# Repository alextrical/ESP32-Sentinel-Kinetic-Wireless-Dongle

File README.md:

# ESP32-Vent-Axia-Sentinel-Kinetic-Wired-Remote-Dongle
ESP32 based Re-implementation of the Vent-Axia Sentinel Kinetic Wired Remote Controller
Arduino sketch can be simulated here
https://wokwi.com/projects/427157112827024385

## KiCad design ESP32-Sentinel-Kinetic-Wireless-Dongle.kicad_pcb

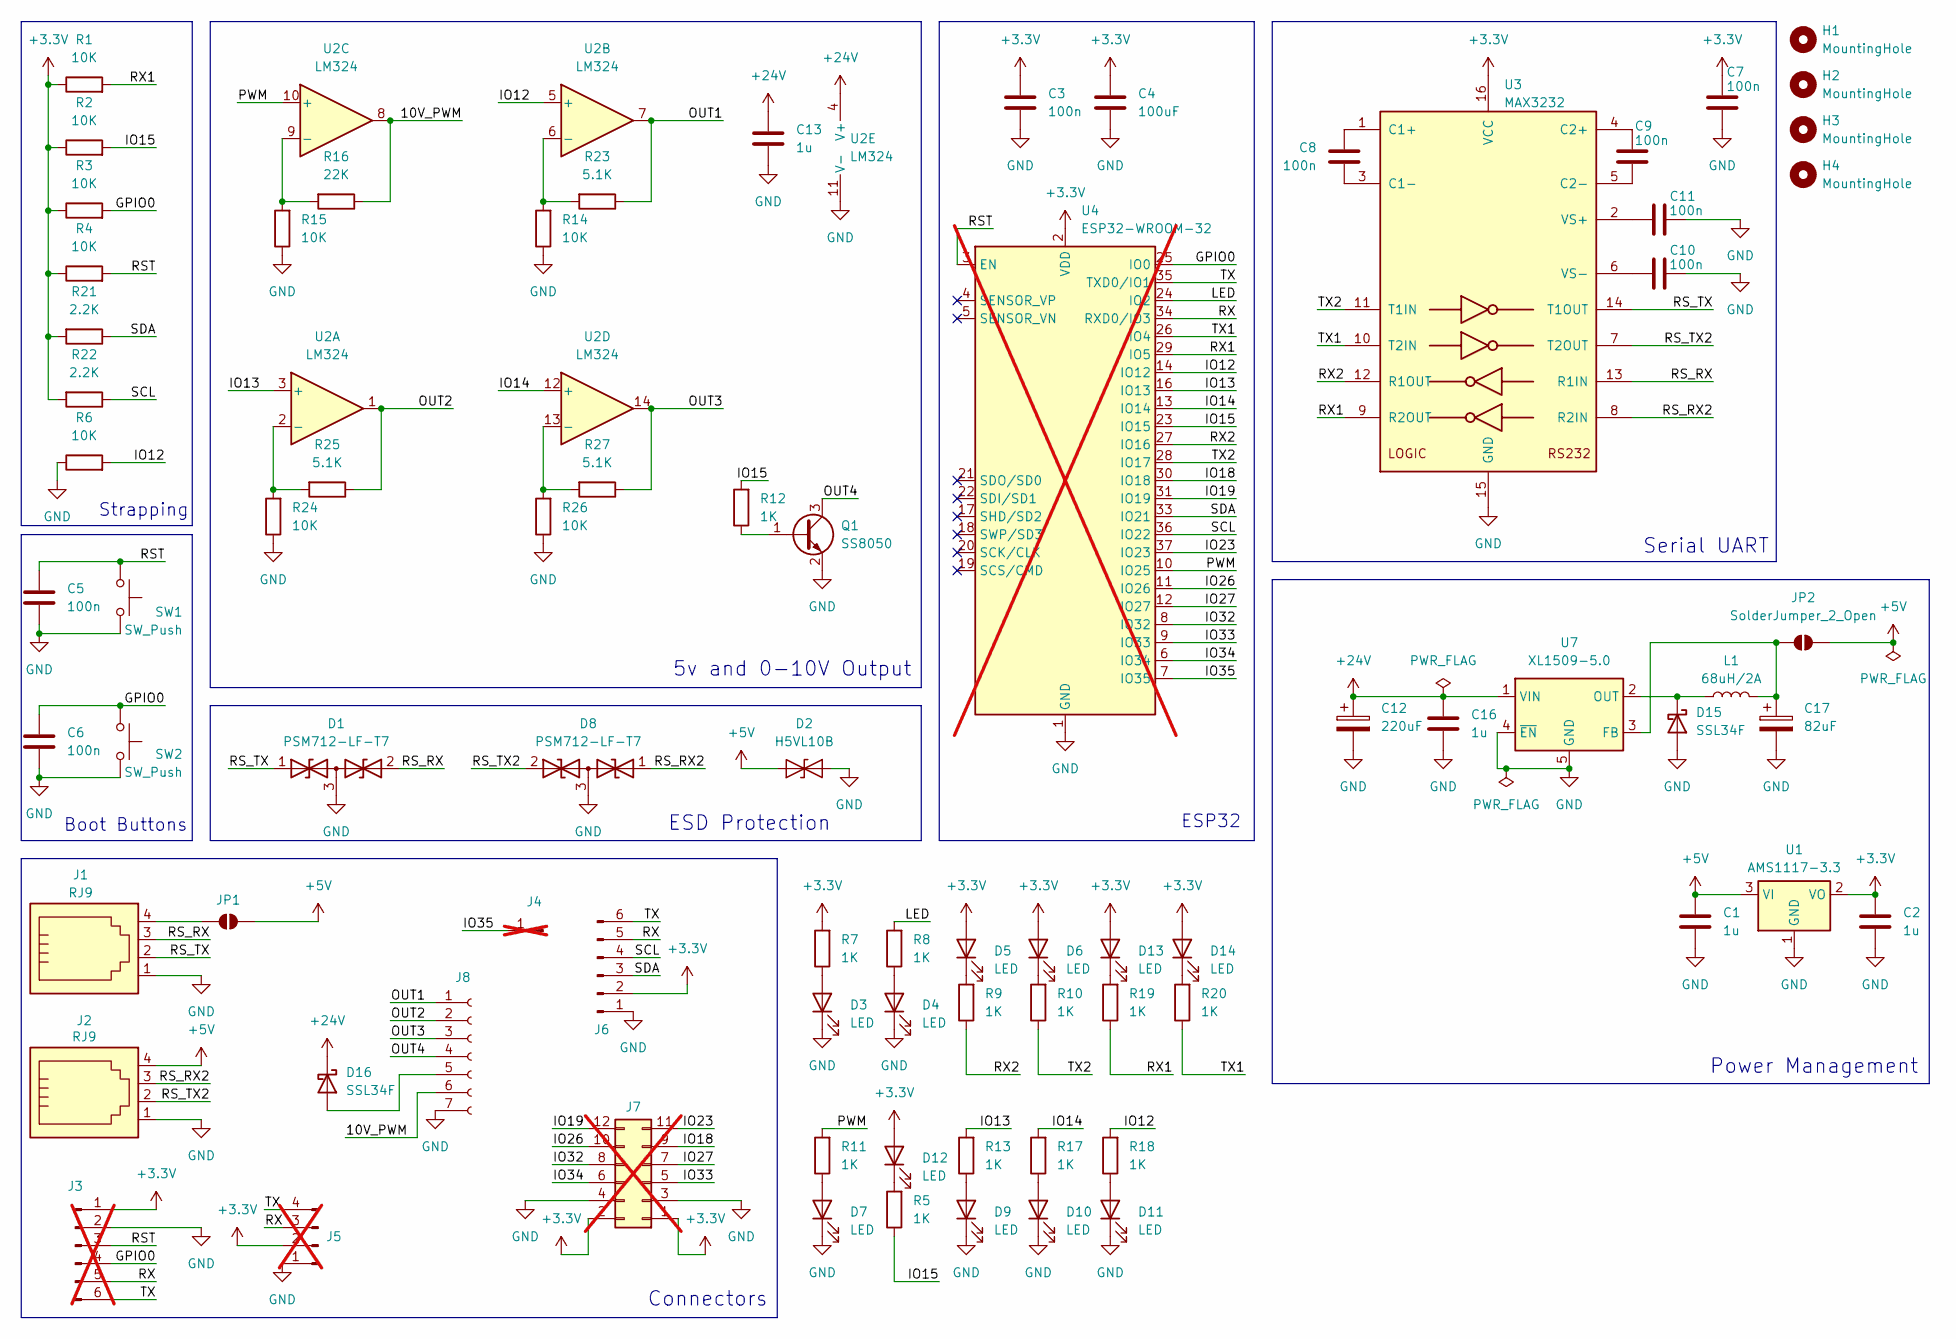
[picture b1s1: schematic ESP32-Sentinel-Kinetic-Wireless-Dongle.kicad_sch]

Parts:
C1, C2: 1u; C_0402_1005Metric; LCSC C52923
C3, C5, C6, C7, C8, C9, C10, C11: 100n; C_0402_1005Metric; LCSC C307331
C4: 100uF; C_1206_3216Metric; LCSC C15008
C12: 220uF; CP_Radial_D10.0mm_P5.00mm
C13, C16: 1u; C_1206_3216Metric; LCSC C1848
C17: 82uF; CP_Radial_D10.0mm_P2.50mm_P5.00mm
D1, D8: PSM712-LF-T7; SOT-23; LCSC C32677
D2: H5VL10B; D_SOD-882; LCSC C7420372
D3, D4, D5, D6, D7, D9, D10, D11, D12, D13, D14: LED; LED_0603_1608Metric; LCSC C2286
D15, D16: SSL34F; D_SMA; LCSC C28646282
H1, H2, H3, H4: MountingHole; MountingHole_3.2mm_M3
J1, J2: RJ9; RJ9-TH-623K-4P4CGRAYBOUNDLESS
J3: Conn_01x06_Pin; PinHeader_1x06_P2.00mm_Vertical_locking; not fitted
J4: Conn_01x01_Pin; PinHeader_1x01_P2.54mm_Vertical; not fitted
J5: Conn_01x04_Pin; PinHeader_1x04_P2.54mm_Vertical; not fitted
J6: Conn_01x06_Pin; JST_XH_B6B-XH-A_1x06_P2.50mm_Vertical
J7: Conn_02x06_Odd_Even; PinHeader_2x06_P2.54mm_Vertical; not fitted
J8: Conn_01x07_Socket; JST_XH_B7B-XH-A_1x07_P2.50mm_Vertical
JP1, JP2: SolderJumper_2_Open; SolderJumper-2_P1.3mm_Open_RoundedPad1.0x1.5mm
L1: 68uH/2A; L_APV_APH0850; LCSC C41415633
Q1: SS8050; SOT-23; LCSC C431710
R1, R2, R3, R4, R6, R14, R15, R24, R26: 10K; R_0402_1005Metric; LCSC C25744
R5, R7, R8, R9, R10, R11, R12, R13, R17, R18, R19, R20: 1K; R_0402_1005Metric; LCSC C11702
R16: 22K; R_0402_1005Metric; LCSC C25768
R21, R22: 2.2K; R_0402_1005Metric; LCSC C25879
R23, R25, R27: 5.1K; R_0402_1005Metric; LCSC C25905
SW1, SW2: SW_Push; SW_Push_1P1T_XKB_TS-1187A; LCSC C318884
U1: AMS1117-3.3; SOT-223-3_TabPin2; LCSC C6186
U2: LM324; SOIC-14_3.9x8.7mm_P1.27mm; LCSC C71035
U3: MAX3232; SOP-16_3.9x9.9mm_P1.27mm; LCSC C5201633
U4: ESP32-WROOM-32; not fitted
U7: XL1509-5.0; SOIC-8_3.9x4.9mm_P1.27mm; LCSC C61063

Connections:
+3.3V: C2.1, C3.1, C4.1, C7.1, D5.2 (A), D6.2 (A), D12.2 (A), D13.2 (A), D14.2 (A), J3.1, J5.2, J6.2, J7.1, J7.2, R1.1, R2.1, R3.1, R4.1, R7.2, R21.2, R22.2, U1.2 (VO), U3.16 (VCC), U4.2 (VDD)
+5V: C1.1, D2.1 (A1), J2.4, JP1.2 (B), JP2.2 (B), U1.3 (VI)
+24V: C12.1, C13.1, C16.1, D16.1 (K), U2.4 (V+), U7.1 (VIN)
/10V_PWM: J8.6, R16.1, U2.8
/GPIO0: C6.1, J3.4, R3.2, SW2.1, U4.25 (IO0)
/IO12: R6.2, R18.2, U2.5 (+), U4.14 (IO12)
/IO13: R13.2, U2.3 (+), U4.16 (IO13)
/IO14: R17.2, U2.12 (+), U4.13 (IO14)
/IO15: R2.2, R5.1, R12.2, U4.23 (IO15)
/IO18: J7.9, U4.30 (IO18)
/IO19: J7.12, U4.31 (IO19)
/IO23: J7.11, U4.37 (IO23)
/IO26: J7.10, U4.11 (IO26)
/IO27: J7.7, U4.12 (IO27)
/IO32: J7.8, U4.8 (IO32)
/IO33: J7.5, U4.9 (IO33)
/IO34: J7.6, U4.6 (IO34)
/IO35: J4.1, U4.7 (IO35)
/LED: R8.2, U4.24 (IO2)
/OUT1: J8.1, R23.1, U2.7
/OUT2: J8.2, R25.1, U2.1
/OUT3: J8.3, R27.1, U2.14
/OUT4: J8.4, Q1.3 (C)
/PWM: R11.2, U2.10 (+), U4.10 (IO25)
/RST: C5.1, J3.3, R4.2, SW1.1, U4.3 (EN)
/RS_RX: D1.2 (A2), J1.3, U3.13 (R1IN)
/RS_RX2: D8.1 (A1), J2.3, U3.8 (R2IN)
/RS_TX: D1.1 (A1), J1.2, U3.14 (T1OUT)
/RS_TX2: D8.2 (A2), J2.2, U3.7 (T2OUT)
/RX: J3.5, J5.3, J6.5, U4.34 (RXD0/IO3)
/RX1: R1.2, R19.1, U3.9 (R2OUT), U4.29 (IO5)
/RX2: R9.1, U3.12 (R1OUT), U4.27 (IO16)
/SCL: J6.4, R22.1, U4.36 (IO22)
/SDA: J6.3, R21.1, U4.33 (IO21)
/TX: J3.6, J5.4, J6.6, U4.35 (TXD0/IO1)
/TX1: R20.1, U3.10 (T2IN), U4.26 (IO4)
/TX2: R10.1, U3.11 (T1IN), U4.28 (IO17)
GND: C1.2, C2.2, C3.2, C4.2, C5.2, C6.2, C7.2, C10.2, C11.2, C12.2, C13.2, C16.2, C17.2, D1.3 (common), D2.2 (A2), D3.1 (K), D4.1 (K), D7.1 (K), D8.3 (common), D9.1 (K), D10.1 (K), D11.1 (K), D15.2 (A), J1.1, J2.1, J3.2, J5.1, J6.1, J7.3, J7.4, J8.7, Q1.2 (E), R6.1, R14.1, R15.1, R24.1, R26.1, SW1.2, SW2.2, U1.1 (GND), U2.11 (V-), U3.15 (GND), U4.1 (GND), U4.15 (GND), U4.38 (GND), U4.39 (GND), U7.4 (~EN), U7.5 (GND), U7.6 (GND), U7.7 (GND), U7.8 (GND)
unnamed: D3.2 (A), R7.1
unnamed: D4.2 (A), R8.1
unnamed: D5.1 (K), R9.2
unnamed: D6.1 (K), R10.2
unnamed: D7.2 (A), R11.1
unnamed: D9.2 (A), R13.1
unnamed: D10.2 (A), R17.1
unnamed: D11.2 (A), R18.1
unnamed: D12.1 (K), R5.2
unnamed: D13.1 (K), R19.2
unnamed: D14.1 (K), R20.2
unnamed: D15.1 (K), L1.1, U7.2 (OUT)
unnamed: D16.2 (A), J8.5
unnamed: J1.4, JP1.1 (A)
unnamed: C17.1, JP2.1 (A), L1.2, U7.3 (FB)
unnamed: Q1.1 (B), R12.1
unnamed: R24.2, R25.2, U2.2 (-)
unnamed: R14.2, R23.2, U2.6 (-)
unnamed: R15.2, R16.2, U2.9 (-)
unnamed: R26.2, R27.2, U2.13 (-)
unnamed: C8.1, U3.1 (C1+)
unnamed: C8.2, U3.3 (C1-)
unnamed: C9.1, U3.4 (C2+)
unnamed: C9.2, U3.5 (C2-)
unnamed: C11.1, U3.2 (VS+)
unnamed: C10.1, U3.6 (VS-)

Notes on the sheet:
ESP32
5v and 0-10V Output
Boot Buttons
Strapping
Power Management
Serial UART
Connectors
ESD Protection

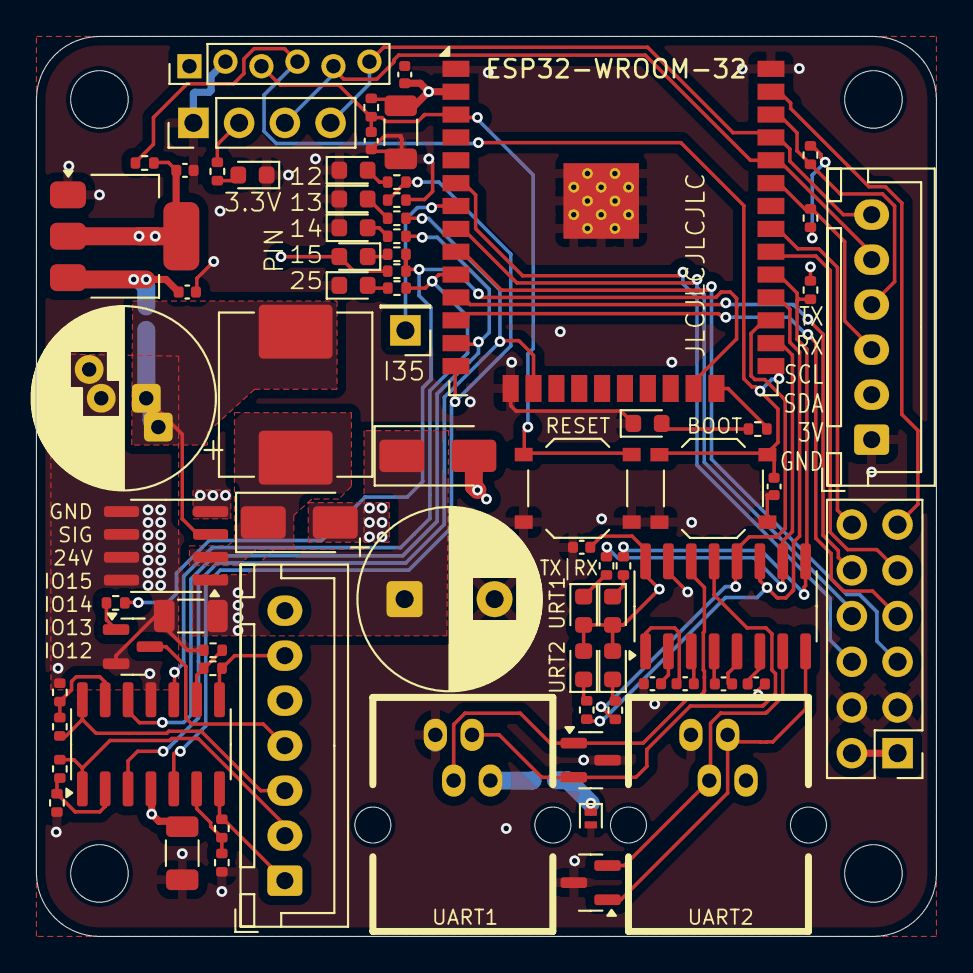
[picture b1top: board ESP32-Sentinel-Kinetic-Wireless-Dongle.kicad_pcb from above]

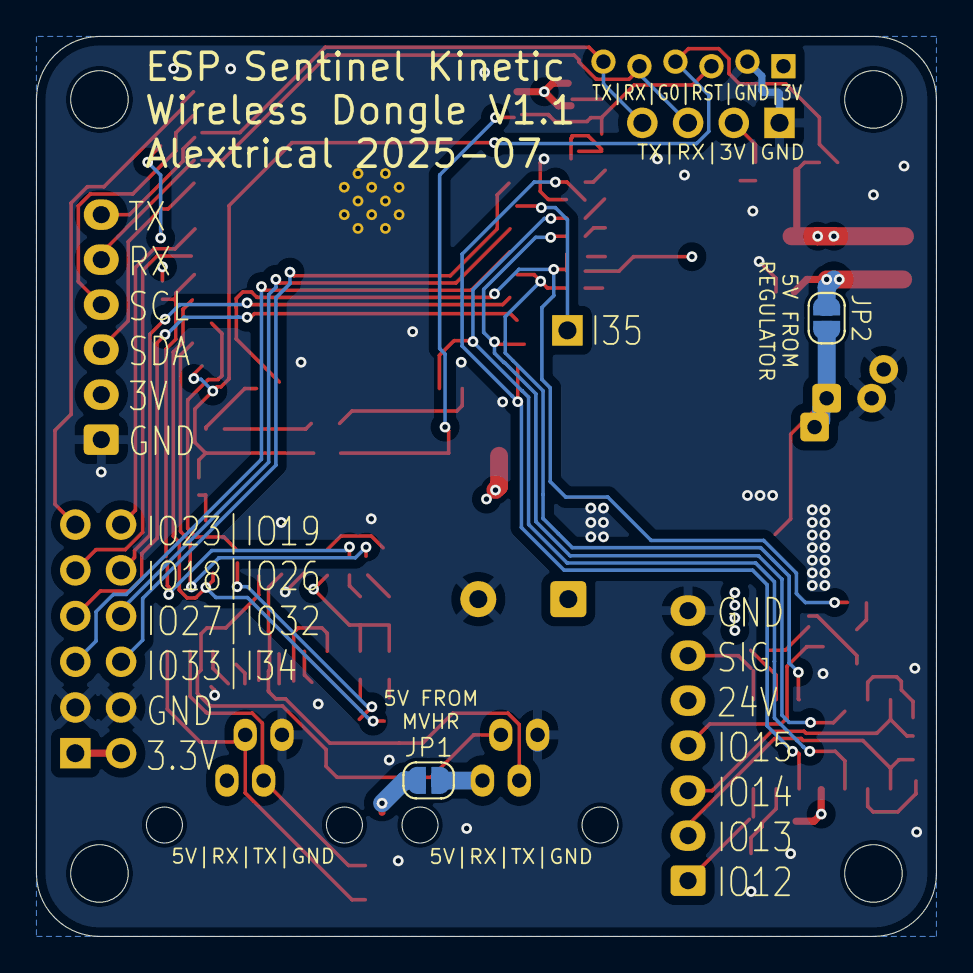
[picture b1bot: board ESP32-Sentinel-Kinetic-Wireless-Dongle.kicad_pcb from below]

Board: 4 copper layers, 50.0 x 50.0 mm, 81 parts (2 on the bottom side), 64 nets.

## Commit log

2025-06-12 Checkin
2025-06-12 Added PDF and OSHW logo
2025-06-18 Completed PCB Layout Added PWM Rail to rail Added Silkscreen markings
2025-06-18 Added LCSC Part Numbers
2025-06-19 corrected rx and tx positions for lilygo downloader
2025-06-21 Include push buttons in BOM
2025-07-05 Added Silkscreen markings to Diagnostic LED's Inverted Serial LED's, so LED is only on when signal is sent or recieved.
2025-07-10 Applied fixes to issues from V1 Inverted LED's on UART to indicate only when data is sent Added Second UART to allow passthrough Removed support for ESP8266
    Still need to add:
    pin breakout for user mods
    Buck regulator from 24V. We need more current on the 5V rail than available, if we expect anything else to be connected up (and not cause a brown out)
2025-07-12 Layout completed Revesed RJ9 pinout to match Display Module Added reverse polarity protection diode to 24V rail Using OpAMP for 3.3 to 5V conversion Using OpAmp for 3.3 to 10V conversion JST XH for M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
2025-07-12 Update PDF schematic
2025-07-14 Renamed Project for ESP32
2025-07-14 Updated LCSC numbers
2025-07-16 Replaced project name references from ESP8266 to ESP32
